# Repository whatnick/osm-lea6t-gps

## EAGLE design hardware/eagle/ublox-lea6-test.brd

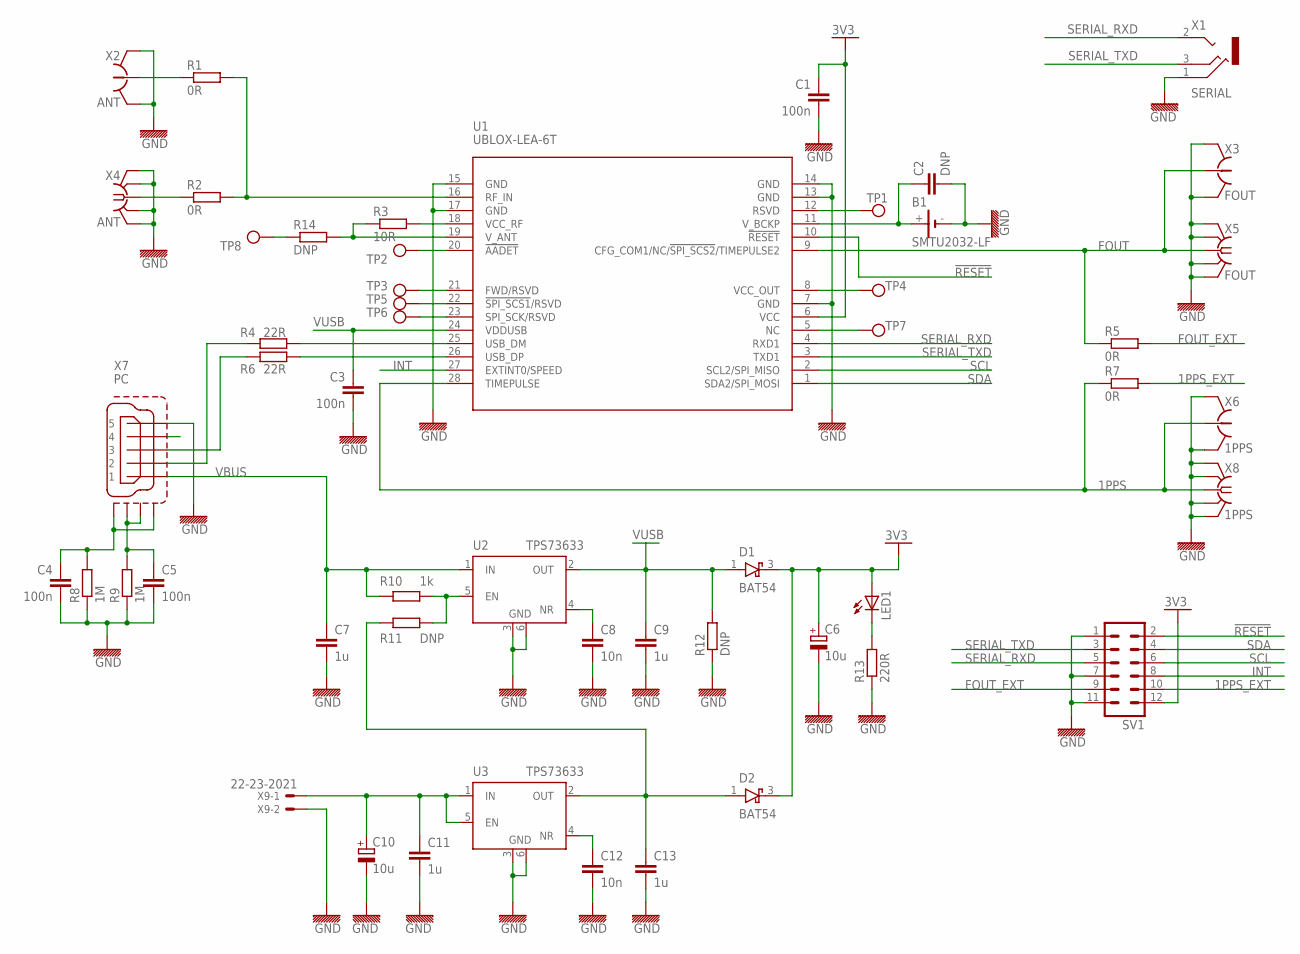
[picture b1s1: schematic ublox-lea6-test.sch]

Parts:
B1: SMTU2032-LF; SMTU2032
C1, C3, C4, C5: 100n; 0603
C2: DNP; 0603
C6, C10: 10u; A/3216-18R
C7, C9, C11, C13: 1u; 0603
C8, C12: 10n; 0603
D1, D2: BAT54; SOT23
LED1: LEDSML0603; SML0603
R1, R2, R5, R7: 0R; 0603
R3: 10R; 0603
R4, R6: 22R; 0603
R8, R9: 1M; 0603
R10: 1k; 0603
R11, R12, R14: DNP; 0603
R13: 220R; 0603
SV1: MA06-2
TP1, TP2, TP3, TP4, TP5, TP6, TP7, TP8: TESTPAD; TP_1X1
U1: UBLOX-LEA-6T; UBLOX-LEA-6
U2, U3: TPS73633; SOT223-6
X1: SERIAL; JACK2.5_SJ-2523
X2: ANT; HRS_UFL
X3: FOUT; HRS_UFL
X4: ANT; SMA-F-S-EDGE
X5: FOUT; SMA-F-S-EDGE
X6: 1PPS; HRS_UFL
X7: PC; UX60-MB-5ST
X8: 1PPS; SMA-F-S-EDGE
X9: 22-23-2021

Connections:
1PPS: R7.1, U1.28 (TIMEPULSE), X6.SIG (1), X8.C (1)
1PPS_EXT: R7.2, SV1.10
3V3: C1.1, C6.+, D1.3 (C), D2.3 (C), LED1.A, SV1.12, U1.6 (VCC)
!RESET: SV1.2, U1.10 (!RESET)
FOUT: R5.1, U1.9 (CFG_COM1/NC/!SPI_SCS2!/TIMEPULSE2), X3.SIG (1), X5.C (1)
FOUT_EXT: R5.2, SV1.9
GND: B1.-, C1.2, C2.2, C3.2, C4.2, C5.2, C6.-, C7.2, C8.2, C9.2, C10.-, C11.2, C12.2, C13.2, R8.1, R9.1, R12.1, R13.1, SV1.1, SV1.7, SV1.11, U1.7 (GND), U1.13 (GND), U1.14 (GND), U1.15 (GND), U1.17 (GND), U2.3 (GND), U2.6 (GND1), U3.3 (GND), U3.6 (GND1), X1.1 (RING), X2.GND@1 (GND), X2.GND@2 (GND), X3.GND@1 (GND), X3.GND@2 (GND), X4.BG1 (GND), X4.BG2 (GND), X4.TG1 (GND), X4.TG2 (GND), X5.BG1 (GND), X5.BG2 (GND), X5.TG1 (GND), X5.TG2 (GND), X6.GND@1 (GND), X6.GND@2 (GND), X7.5, X8.BG1 (GND), X8.BG2 (GND), X8.TG1 (GND), X8.TG2 (GND), X9.2
INT: SV1.8, U1.27 (EXTINT0/SPEED)
unnamed: R2.1, X4.C (1)
unnamed: C4.1, R8.2, X7.M1 (S1), X7.M4 (S4)
unnamed: R4.2, U1.25 (USB_DM)
unnamed: R6.2, U1.26 (USB_DP)
unnamed: R3.2, U1.18 (VCC_RF)
unnamed: R3.1, R14.2, U1.19 (V_ANT)
unnamed: TP3.TP, U1.21 (FWD/RSVD)
unnamed: TP2.TP, U1.20 (!AADET)
unnamed: TP5.TP, U1.22 (!SPI_SCS1!/RSVD)
unnamed: TP6.TP, U1.23 (SPI_SCK/RSVD)
unnamed: R6.1, X7.3
unnamed: R4.1, X7.2
unnamed: C8.1, U2.4 (NR)
unnamed: TP1.TP, U1.12 (RSVD)
unnamed: B1.+, C2.1, U1.11 (V_BCKP)
unnamed: R1.1, X2.SIG (1)
unnamed: TP4.TP, U1.8 (VCC_OUT)
unnamed: TP7.TP, U1.5 (NC)
unnamed: R1.2, R2.2, U1.16 (RF_IN)
unnamed: C5.1, R9.2, X7.M2 (S2), X7.M3 (S3)
unnamed: C10.+, C11.1, U3.1 (IN), U3.5 (EN), X9.1
unnamed: C12.1, U3.4 (NR)
unnamed: C13.1, D2.1 (A), R11.1, U3.2 (OUT)
unnamed: R10.2, R11.2, U2.5 (EN)
unnamed: LED1.C, R13.2
unnamed: R14.1, TP8.TP
SCL: SV1.6, U1.2 (SCL2/SPI_MISO)
SDA: SV1.4, U1.1 (SDA2/SPI_MOSI)
SERIAL_RXD: SV1.5, U1.4 (RXD1), X1.2 (TIP)
SERIAL_TXD: SV1.3, U1.3 (TXD1), X1.3 (MIDDLE)
VBUS: C7.1, R10.1, U2.1 (IN), X7.1
VUSB: C3.1, C9.1, D1.1 (A), R12.2, U1.24 (VDDUSB), U2.2 (OUT)

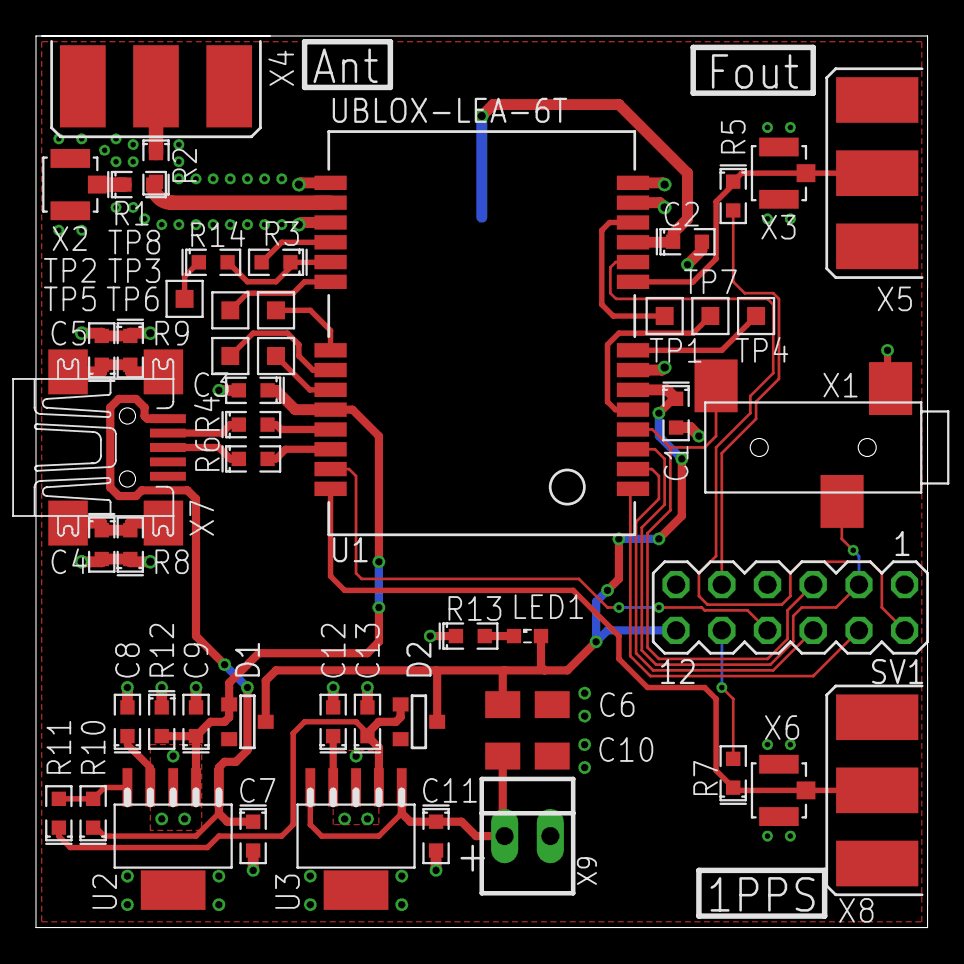
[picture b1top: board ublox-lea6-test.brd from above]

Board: 2 copper layers, 49.5 x 49.5 mm, 52 parts (1 on the bottom side), 40 nets.

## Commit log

2012-04-27 add ublox LEA6T evaluation board design, first version
2012-04-27 don't have two SERIAL_RXD labels but one RXD and one TXD
2012-04-27 sylvains branch (ignores some of harald's changes)
2012-04-27 re-merge my previous changes manually into the project
2012-04-27 approve various ERC changes
2012-07-12 add updated PDF schematics
2013-03-13 update the _brd.pdf to include the LED and R13 and correspond with schemstics
2013-11-24 remove D45014F marking (seeedstudio)
2013-11-24 add CAM file for generating gerber output
2013-11-24 import gerber output
2014-11-17 Fixed up values and polygon signal

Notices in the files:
hardware/eagle/ublox-lea6-test.brd:
(c) 2012 Munaut
